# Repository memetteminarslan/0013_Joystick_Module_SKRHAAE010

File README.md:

# 0013_Joystick_Module_SKRHAAE010
You are seeing a large number of widely used Joystick modules in electronic development kits. More information coming soon...

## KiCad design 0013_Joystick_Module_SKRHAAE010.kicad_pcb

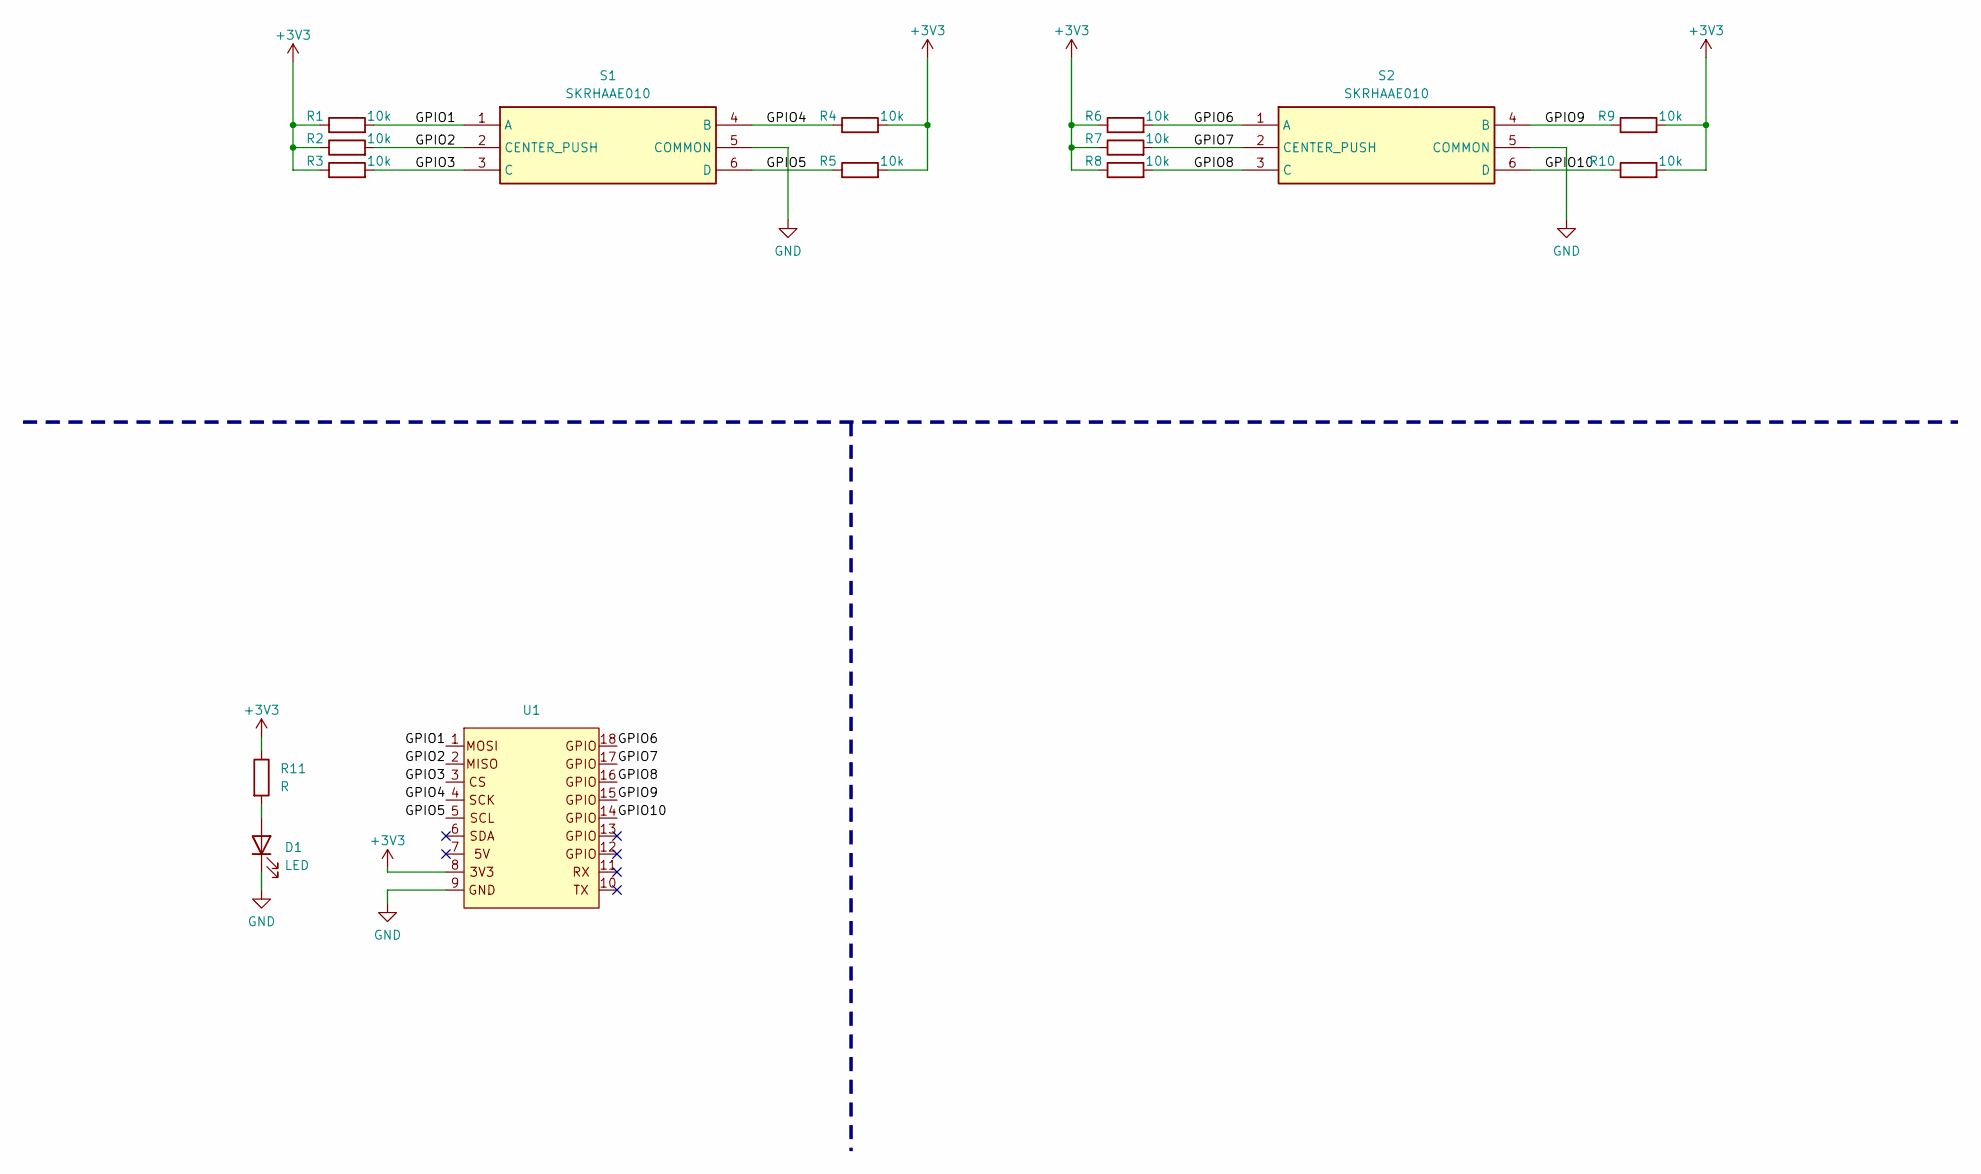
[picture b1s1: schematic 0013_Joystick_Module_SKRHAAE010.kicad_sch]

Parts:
D1: LED; LED_0805_2012Metric
R1, R2, R3, R4, R5, R6, R7, R8, R9, R10: 10k; R_0805_2012Metric
R11: R; R_0805_2012Metric
S1, S2: SKRHAAE010; Mouser Part Number 688-SKRHAAE010
U1: pin_header

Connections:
+3V3: R1.1, R2.1, R3.1, R4.2, R5.2, R6.1, R7.1, R8.1, R9.2, R10.2, R11.1, U1.8
/GPIO1: R1.2, S1.1 (A), U1.1
/GPIO2: R2.2, S1.2 (CENTER_PUSH), U1.2
/GPIO3: R3.2, S1.3 (C), U1.3
/GPIO4: R4.1, S1.4 (B), U1.4
/GPIO5: R5.1, S1.6 (D), U1.5
/GPIO6: R6.2, S2.1 (A), U1.18
/GPIO7: R7.2, S2.2 (CENTER_PUSH), U1.17
/GPIO8: R8.2, S2.3 (C), U1.16
/GPIO9: R9.1, S2.4 (B), U1.15
/GPIO10: R10.1, S2.6 (D), U1.14
GND: D1.1 (K), S1.5 (COMMON), S2.5 (COMMON), U1.9
unnamed: D1.2 (A), R11.2

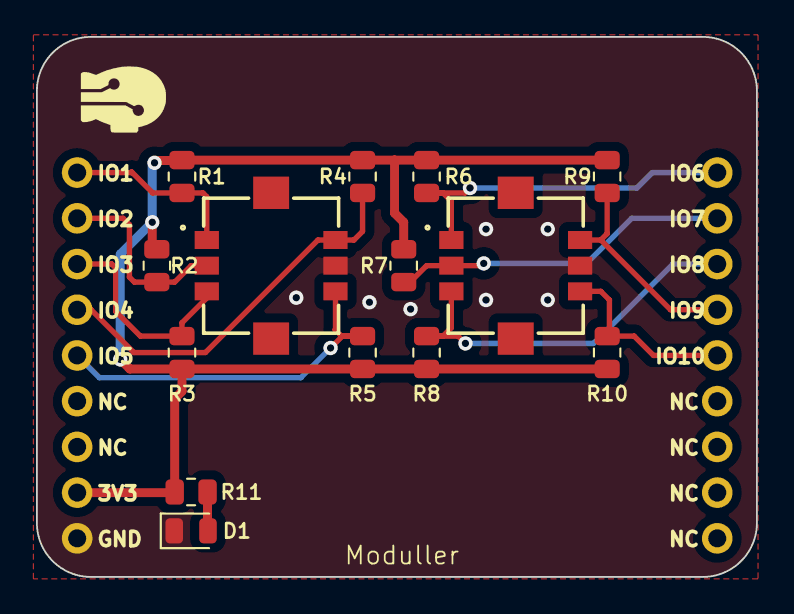
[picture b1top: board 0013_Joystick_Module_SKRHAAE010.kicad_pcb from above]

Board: 2 copper layers, 40.0 x 30.0 mm, 15 parts (0 on the bottom side), 13 nets.
